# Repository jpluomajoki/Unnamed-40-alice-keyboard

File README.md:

# Unnamed 40% alice keyboard
40% Alice-ish keyboard. Work in progress!
Working title is Liisa, the finnish translation for alice.

The PCB should fit and mount within a standard 60% case.

[Layout in KLE](http://www.keyboard-layout-editor.com/#/gists/e5abee241ba44cb635d8e97dbdc8999b)

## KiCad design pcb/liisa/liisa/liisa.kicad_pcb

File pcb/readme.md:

Here is the folder for the pcb created in kicad.

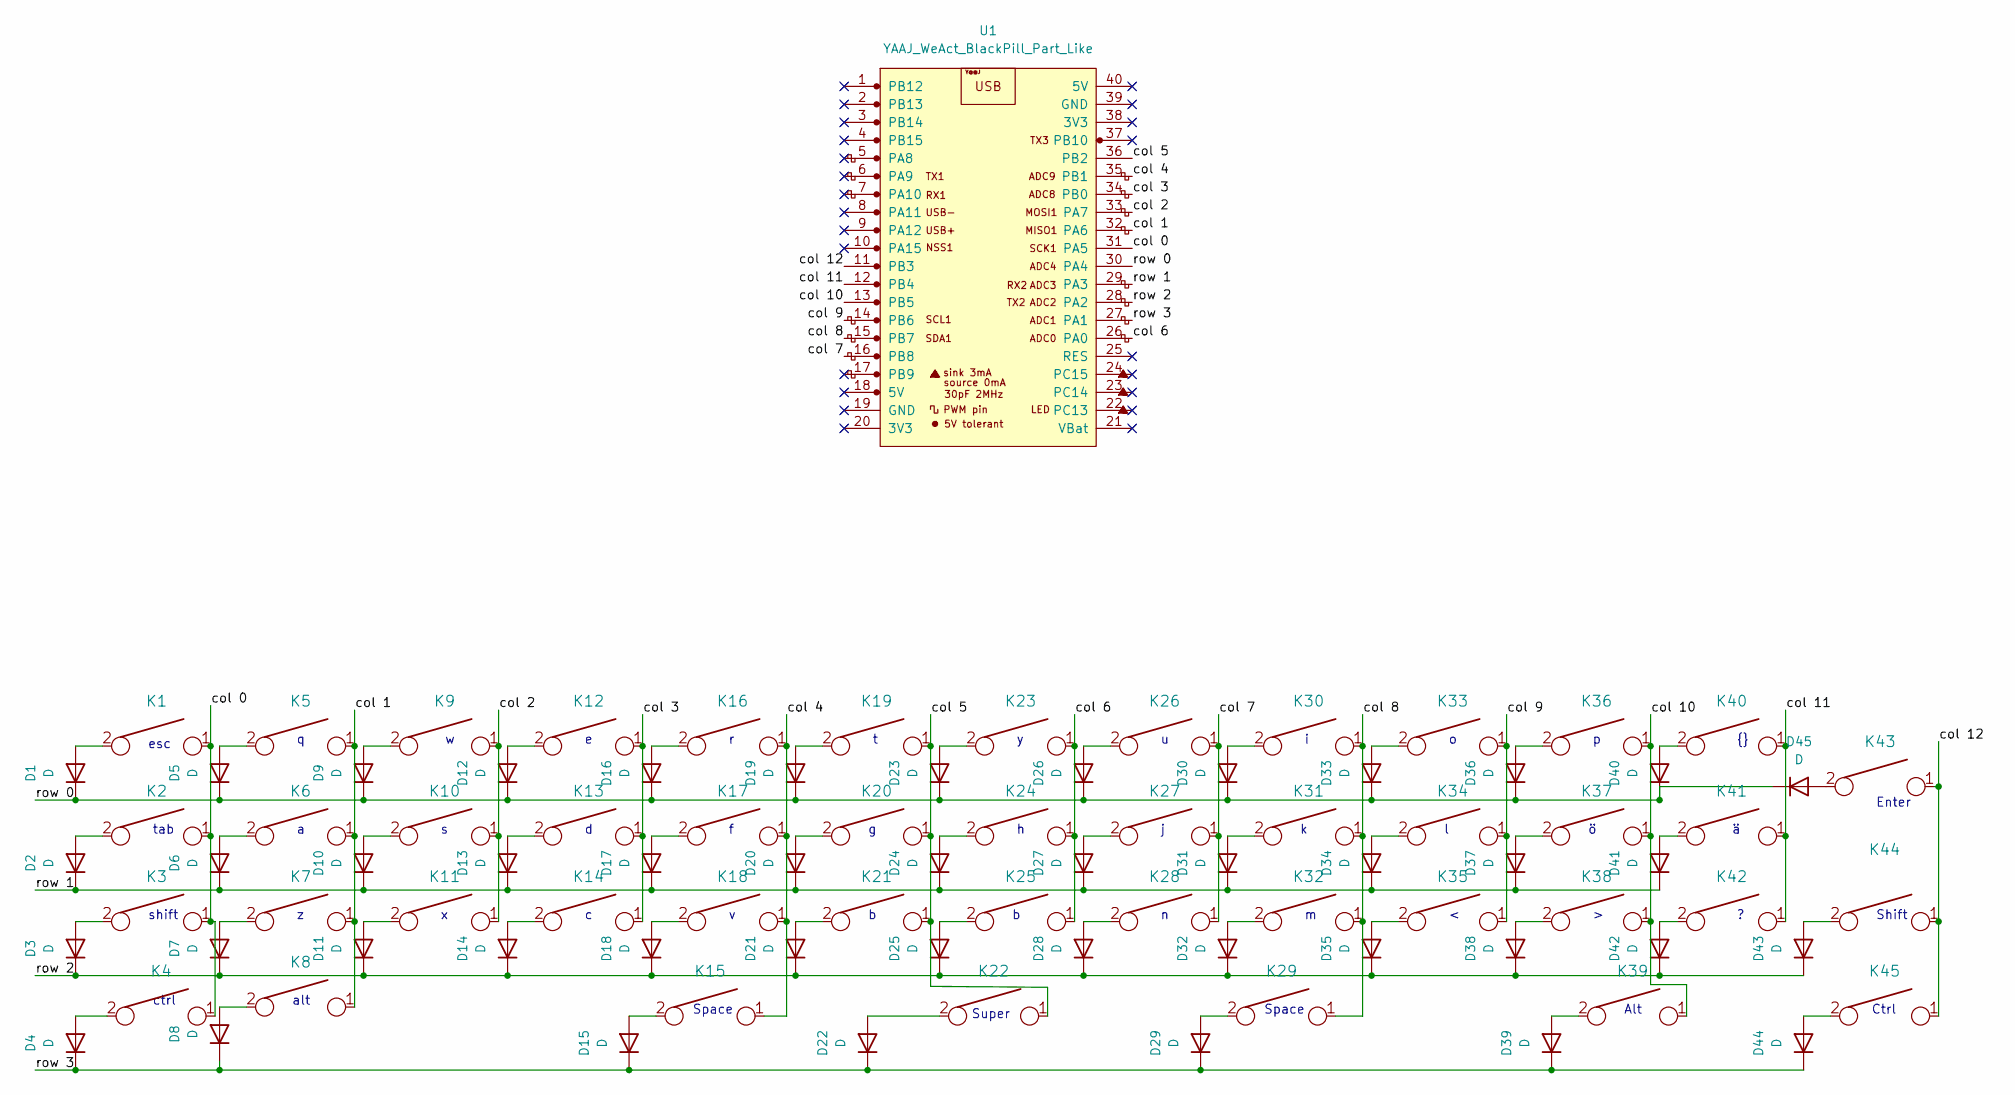
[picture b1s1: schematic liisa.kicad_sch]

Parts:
D1, D2, D3, D4, D5, D6, D7, D8, D9, D10, D11, D12, D13, D14, D15, D16, D17, D18, D19, D20, D21, D22, D23, D24, D25, D26, D27, D28, D29, D30, D31, D32, D33, D34, D35, D36, D37, D38, D39, D40, D41, D42, D43, D44, D45: D; D_SOD-123F
K1, K5, K6, K7, K9, K10, K11, K12, K13, K14, K16, K17, K18, K19, K20, K21, K22, K23, K24, K25, K26, K27, K28, K30, K31, K32, K33, K34, K35, K36, K37, K38, K40, K41, K42: KEYSW; Mx_Alps_100
K2, K4, K8, K39, K45: KEYSW; Mx_Alps_125
K3, K44: KEYSW; Mx_Alps_150
K15: KEYSW; Mx_Alps_225
K29: KEYSW; Mx_Alps_275
K43: KEYSW; Mx_Alps_200
U1: YAAJ_WeAct_BlackPill_Part_Like; YAAJ_WeAct_BlackPill_2

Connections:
/col 0: K1.1, K2.1, K3.1, K4.1, U1.31 (PA5)
/col 1: K5.1, K6.1, K7.1, K8.1, U1.32 (PA6)
/col 2: K9.1, K10.1, K11.1, U1.33 (PA7)
/col 3: K12.1, K13.1, K14.1, U1.34 (PB0)
/col 4: K15.1, K16.1, K17.1, K18.1, U1.35 (PB1)
/col 5: K19.1, K20.1, K21.1, K22.1, U1.36 (PB2)
/col 6: K23.1, K24.1, K25.1, U1.26 (PA0)
/col 7: K26.1, K27.1, K28.1, U1.16 (PB8)
/col 8: K29.1, K30.1, K31.1, K32.1, U1.15 (PB7)
/col 9: K33.1, K34.1, K35.1, U1.14 (PB6)
/col 10: K36.1, K37.1, K38.1, K39.1, U1.13 (PB5)
/col 11: K40.1, K41.1, K42.1, U1.12 (PB4)
/col 12: K43.1, K44.1, K45.1, U1.11 (PB3)
/row 0: D1.1 (K), D5.1 (K), D9.1 (K), D12.1 (K), D16.1 (K), D19.1 (K), D23.1 (K), D26.1 (K), D30.1 (K), D33.1 (K), D36.1 (K), D40.1 (K), D45.1 (K), U1.30 (PA4)
/row 1: D2.1 (K), D6.1 (K), D10.1 (K), D13.1 (K), D17.1 (K), D20.1 (K), D24.1 (K), D27.1 (K), D31.1 (K), D34.1 (K), D37.1 (K), D41.1 (K), U1.29 (PA3)
/row 2: D3.1 (K), D7.1 (K), D11.1 (K), D14.1 (K), D18.1 (K), D21.1 (K), D25.1 (K), D28.1 (K), D32.1 (K), D35.1 (K), D38.1 (K), D42.1 (K), D43.1 (K), U1.28 (PA2)
/row 3: D4.1 (K), D8.1 (K), D15.1 (K), D22.1 (K), D29.1 (K), D39.1 (K), D44.1 (K), U1.27 (PA1)
unnamed: D1.2 (A), K1.2
unnamed: D2.2 (A), K2.2
unnamed: D3.2 (A), K3.2
unnamed: D4.2 (A), K4.2
unnamed: D5.2 (A), K5.2
unnamed: D6.2 (A), K6.2
unnamed: D7.2 (A), K7.2
unnamed: D8.2 (A), K8.2
unnamed: D9.2 (A), K9.2
unnamed: D10.2 (A), K10.2
unnamed: D11.2 (A), K11.2
unnamed: D12.2 (A), K12.2
unnamed: D13.2 (A), K13.2
unnamed: D14.2 (A), K14.2
unnamed: D15.2 (A), K15.2
unnamed: D16.2 (A), K16.2
unnamed: D17.2 (A), K17.2
unnamed: D18.2 (A), K18.2
unnamed: D19.2 (A), K19.2
unnamed: D20.2 (A), K20.2
unnamed: D21.2 (A), K21.2
unnamed: D22.2 (A), K22.2
unnamed: D23.2 (A), K23.2
unnamed: D24.2 (A), K24.2
unnamed: D25.2 (A), K25.2
unnamed: D26.2 (A), K26.2
unnamed: D27.2 (A), K27.2
unnamed: D28.2 (A), K28.2
unnamed: D29.2 (A), K29.2
unnamed: D30.2 (A), K30.2
unnamed: D31.2 (A), K31.2
unnamed: D32.2 (A), K32.2
unnamed: D33.2 (A), K33.2
unnamed: D34.2 (A), K34.2
unnamed: D35.2 (A), K35.2
unnamed: D36.2 (A), K36.2
unnamed: D37.2 (A), K37.2
unnamed: D38.2 (A), K38.2
unnamed: D39.2 (A), K39.2
unnamed: D40.2 (A), K40.2
unnamed: D41.2 (A), K41.2
unnamed: D42.2 (A), K42.2
unnamed: D43.2 (A), K44.2
unnamed: D44.2 (A), K45.2
unnamed: D45.2 (A), K43.2

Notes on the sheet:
Space
esc
alt
Ctrl
Enter
shift
tab
Alt
Shift
ctrl
Super

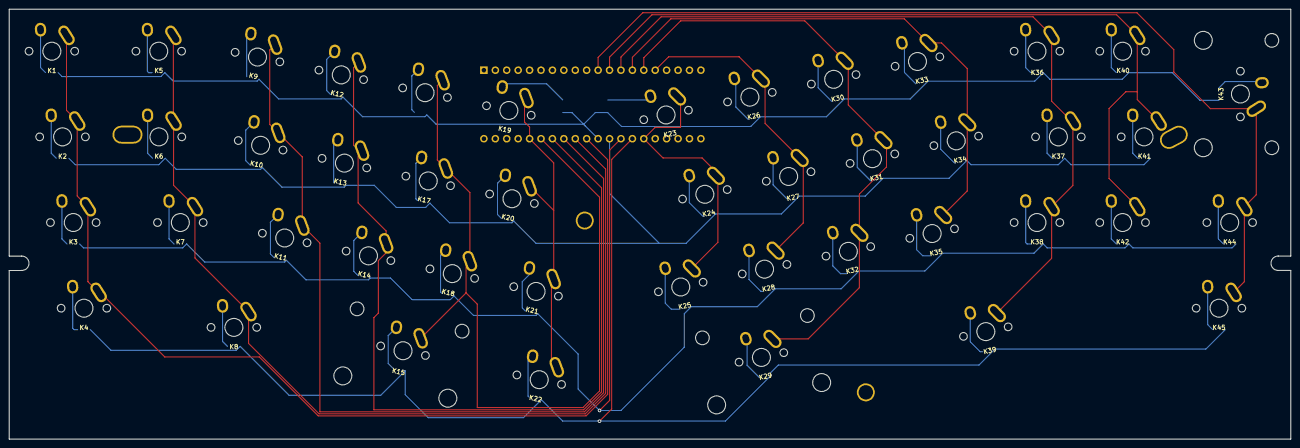
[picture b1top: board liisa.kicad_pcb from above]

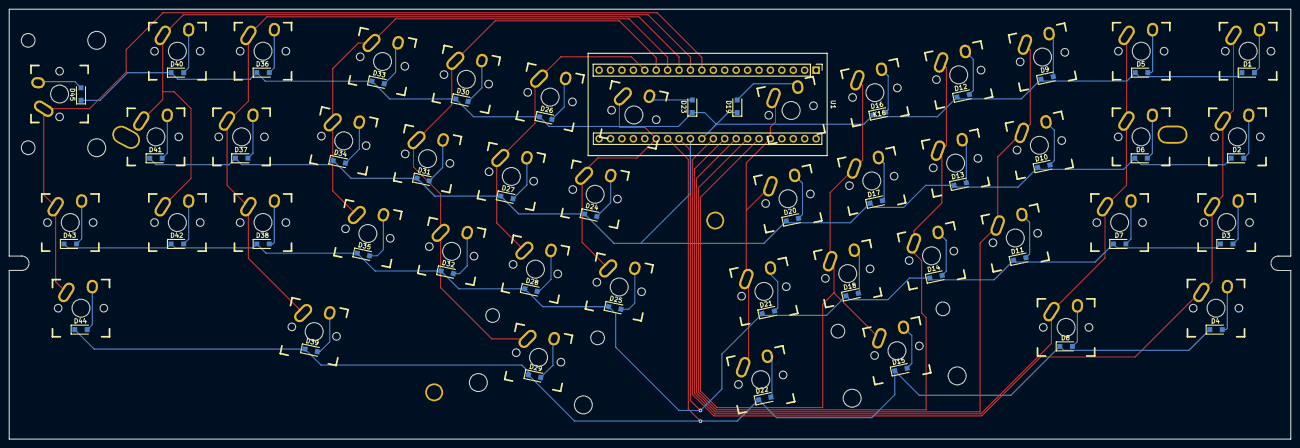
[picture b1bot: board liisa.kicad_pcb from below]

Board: 2 copper layers, 285.0 x 95.6 mm, 95 parts (91 on the bottom side), 62 nets.

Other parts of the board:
HOLE_M3, HOLE_M3#2, HOLE_M3#3, HOLE_M3#4: VAL**; HOLE_M3

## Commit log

2022-07-07 Create readme.md for pcb.
2022-07-07 Add PCB made in kicad
2022-07-10 Update keyboard, add gerbers.
2022-08-19 add qmk
2022-08-19 clean folder structure
